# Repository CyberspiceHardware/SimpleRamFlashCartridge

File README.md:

# Simple Ram Flash Cartridge 

This is a simple ROM/RAM/Flash cartridge for a BBC Master or Acorn Electron.

It takes a single 32K memory device. For example an AS6C62256 or a AT28C256.

# Jumpers / Links

There are three jumpers

J2 - This selects whether the cartridge is for the Master or Electron. It selects the R/WR source from the edge connector.
J3 - This selects whether pin 27 is A14 or nWE. It is typically A14 for (E(P))ROM but nWE for SRAM or Flash.
J4 - This selects whether pin 1 is A14 or 5V. It is typically A14 for SRAM or Flash and 5V (VPP) for (E(P))ROM

You may omit J3 if you want to use a 27C128 EPROM chip where pin 27 is the nPGM pin.

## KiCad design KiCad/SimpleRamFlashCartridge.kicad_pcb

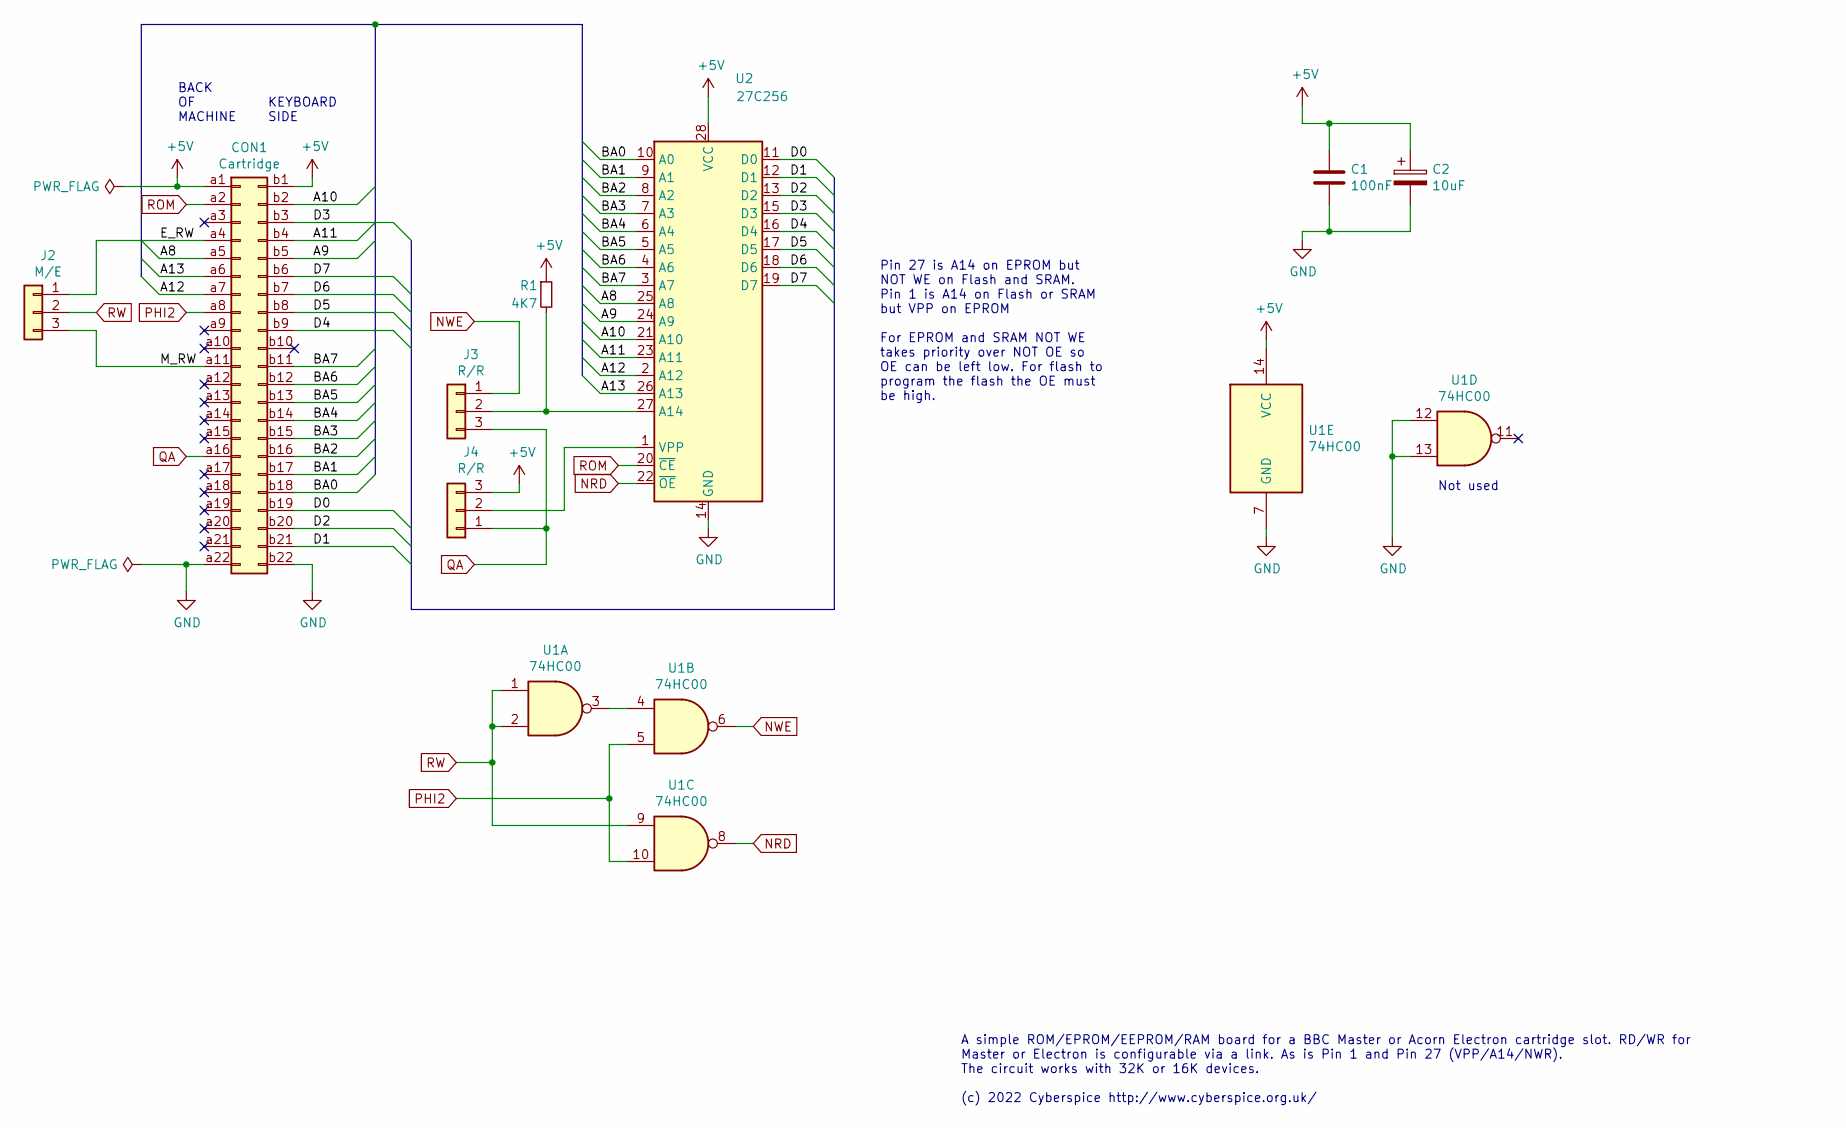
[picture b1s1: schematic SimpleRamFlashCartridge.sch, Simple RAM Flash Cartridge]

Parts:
C1: 100nF; C_Disc_D7.5mm_W2.5mm_P5.00mm
C2: 10uF; CP_Radial_D5.0mm_P2.50mm
CON1: Cartridge; ElectronCartridgeEdge
J2: M/E; PinHeader_1x03_P2.54mm_Vertical
J3, J4: R/R; PinHeader_1x03_P2.54mm_Vertical
R1: 4K7; R_Axial_DIN0204_L3.6mm_D1.6mm_P7.62mm_Horizontal
U1: 74HC00; DIP-14_W7.62mm_Socket
U2: 27C256; DIP-28_W15.24mm_Socket

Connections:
+5V: C1.1, C2.1, CON1.a1, CON1.b1, J4.3, R1.1, U1.14 (VCC), U2.28 (VCC)
/A8: CON1.a5, U2.25 (A8)
/A9: CON1.b5, U2.24 (A9)
/A10: CON1.b2, U2.21 (A10)
/A11: CON1.b4, U2.23 (A11)
/A12: CON1.a7, U2.2 (A12)
/A13: CON1.a6, U2.26 (A13)
/BA0: CON1.b18, U2.10 (A0)
/BA1: CON1.b17, U2.9 (A1)
/BA2: CON1.b16, U2.8 (A2)
/BA3: CON1.b15, U2.7 (A3)
/BA4: CON1.b14, U2.6 (A4)
/BA5: CON1.b13, U2.5 (A5)
/BA6: CON1.b12, U2.4 (A6)
/BA7: CON1.b11, U2.3 (A7)
/D0: CON1.b19, U2.11 (D0)
/D1: CON1.b21, U2.12 (D1)
/D2: CON1.b20, U2.13 (D2)
/D3: CON1.b3, U2.15 (D3)
/D4: CON1.b9, U2.16 (D4)
/D5: CON1.b8, U2.17 (D5)
/D6: CON1.b7, U2.18 (D6)
/D7: CON1.b6, U2.19 (D7)
/E_RW: CON1.a4, J2.1
/M_RW: CON1.a11, J2.3
GND: C1.2, C2.2, CON1.a22, CON1.b22, U1.7 (GND), U1.12, U1.13, U2.14 (GND)
NRD: U1.8, U2.22 (~OE)
NWE: J3.1, U1.6
unnamed: J3.2, R1.2, U2.27 (A14)
unnamed: J4.2, U2.1 (VPP)
unnamed: U1.3, U1.4
PHI2: CON1.a8, U1.5, U1.10
QA: CON1.a16, J3.3, J4.1
ROM: CON1.a2, U2.20 (~CE)
RW: J2.2, U1.1, U1.2, U1.9

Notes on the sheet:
BACK OF MACHINE
KEYBOARD SIDE
Pin 27 is A14 on EPROM but NOT WE on Flash and SRAM. Pin 1 is A14 on Flash or SRAM but VPP on EPROM For EPROM and SRAM NOT WE takes priority over NOT OE so OE can be left low. For flash to program the flash the OE must be high.
Not used
A simple ROM/EPROM/EEPROM/RAM board for a BBC Master or Acorn Electron cartridge slot. RD/WR for Master or Electron is configurable via a link. As is Pin 1 and Pin 27 (VPP/A14/NWR). The circuit works with 32K or 16K devices. (c) 2022 Cyberspice http://www.cyberspice.org.uk/

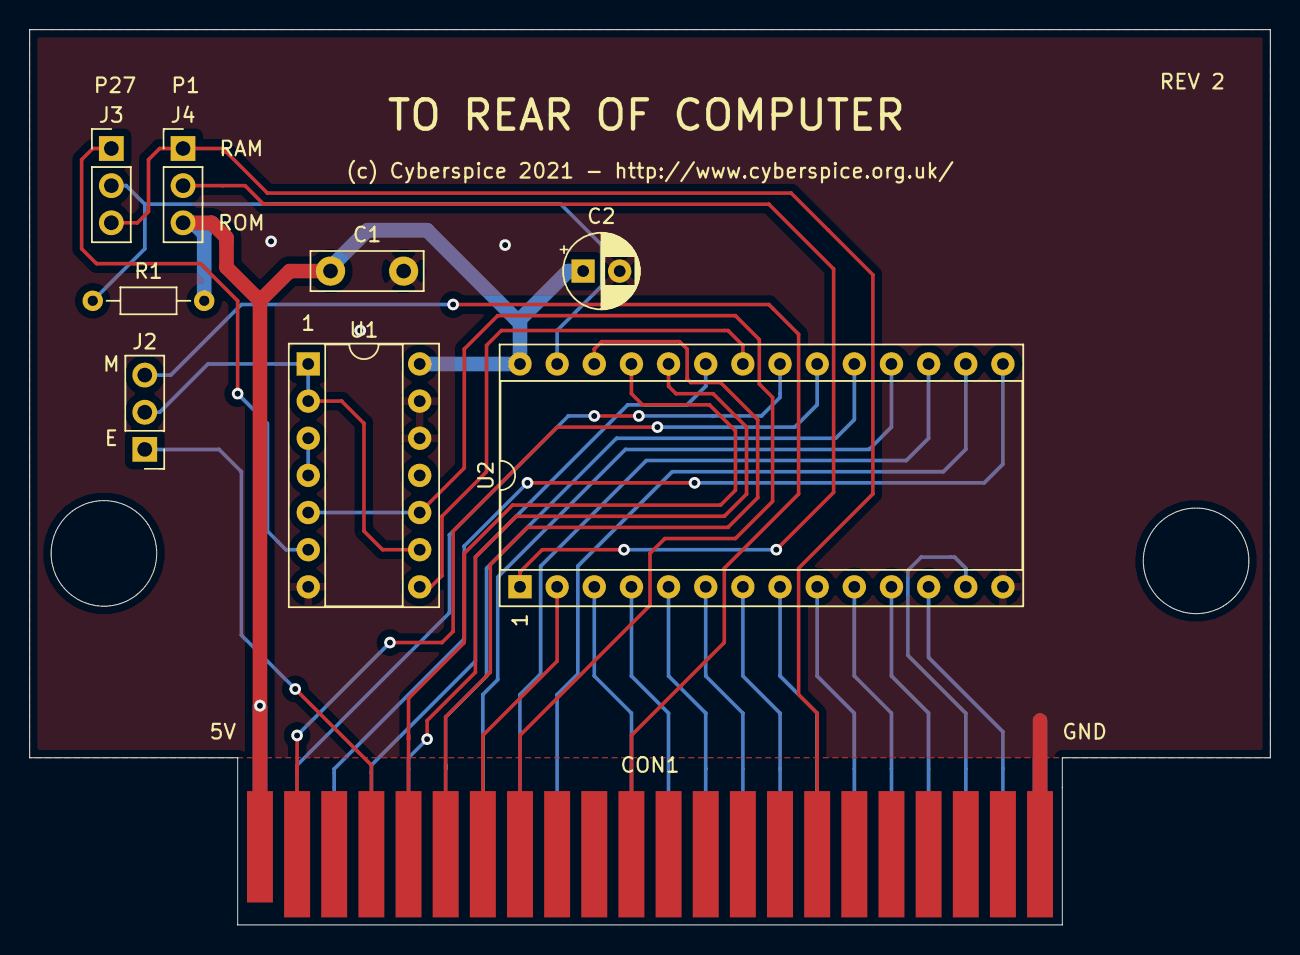
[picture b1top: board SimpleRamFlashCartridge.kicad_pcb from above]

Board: 2 copper layers, 84.8 x 61.2 mm, 9 parts (0 on the bottom side), 35 nets.

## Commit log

2022-01-26 Initial version
2022-01-29 Fixed swapping of A10 and A11. Added gerbers and schematics PDF.
